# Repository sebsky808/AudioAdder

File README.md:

# AudioAdder

The AudioAdder is a PCB designed to combine 4+ 3.5mm TRRS jacks by connecting each of the 4 channels from each port. The unique gimmick of this design is that a near infinite number of combined ports can be achieved by soldering multiple AudioAdder boards together, which in short, means they can be chained together!  The 4x1 pinholes mirror their pinout to prevent soldering errors, and 2 rows of pin headers per side increases overall durability. Additionally, the edge pins can also be used to probe each channel with an oscilloscope.

**NOTE:** Silkscreen labels for each channel follow OMTP/Nokia convention.

## Components
* PJ320-D 3.5mm TRRS barrel (x4 per board)
* 1x4 pin headers (x2/x4 per board) (optional)

## Example Configurations
Due to how common and versatile 3.5mm jacks are, there are a wide range of configurations
for the AudioAdder. Here are just a few!
### 2+ computers and 1+ speaker/headphones
Play audio from 2 or more computers on 1 or more speakers/headphones.
### 2+ GameBoys and a computer
Mix 2 or more Gameboys running Little Sound DJ while recording on a computer.
### An oscilloscope, a computer, and speakers/headphones
Use an oscilloscope to probe audio on each channel while listening to
the audio to get a live look at the waveform of what you are listening to!

## License
Licensed under the [TAPR Open Hardware License](www.tapr.org/OHL)

## Credits
* **Schematics & board designs:** [sebsky808](https://github.com/sebsky808)

## Special Thanks
* **Designed with:** [KiCAD](https://www.kicad.org/)

## Support
If you find this project interesting or helpful, consider supporting me on [ko-fi](https://ko-fi.com/sebsky808), it would be much appreciated!

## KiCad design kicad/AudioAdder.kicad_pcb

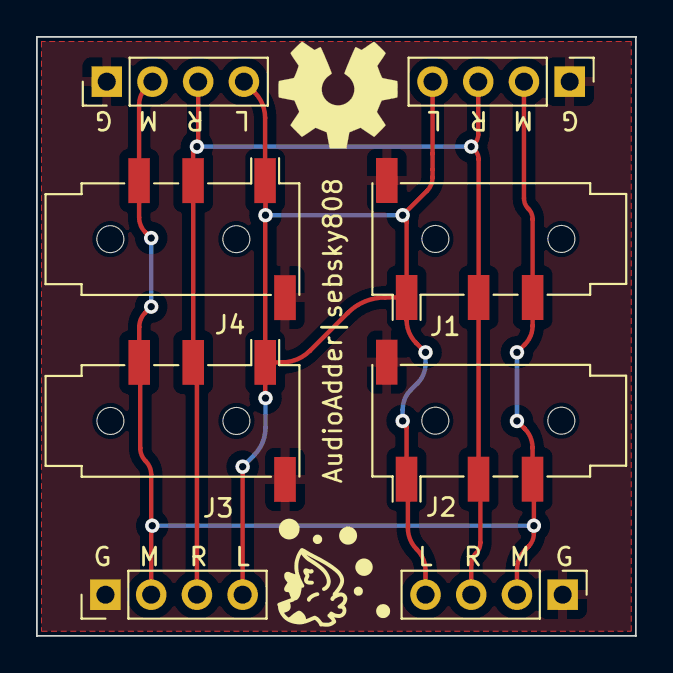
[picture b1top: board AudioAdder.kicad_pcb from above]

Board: 2 copper layers, 33.3 x 33.3 mm, 5 parts (0 on the bottom side), 4 nets.

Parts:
Header 1: PinHeader_1x04_P2.54mm_Vertical
J1, J2, J3, J4: AudioJack4; Jack_3.5mm_PJ320D_Horizontal

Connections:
Ground: Header 1.1, J1.S, J2.S, J3.S, J4.S
Left Ch.: Header 1.4, J1.T, J2.T, J3.T, J4.T
Microphone: Header 1.2, J1.R2, J2.R2, J3.R2, J4.R2
Right Ch.: Header 1.3, J1.R1, J2.R1, J3.R1, J4.R1

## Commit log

2023-11-29 Added CONTRIB.md
